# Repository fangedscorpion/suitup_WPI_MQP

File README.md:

# suitup_WPI_MQP
Repo for the WPI MQP project for Chas Frick, Matt Beardsley, Samee Swartz, Will Barnard, Amanda Adkins

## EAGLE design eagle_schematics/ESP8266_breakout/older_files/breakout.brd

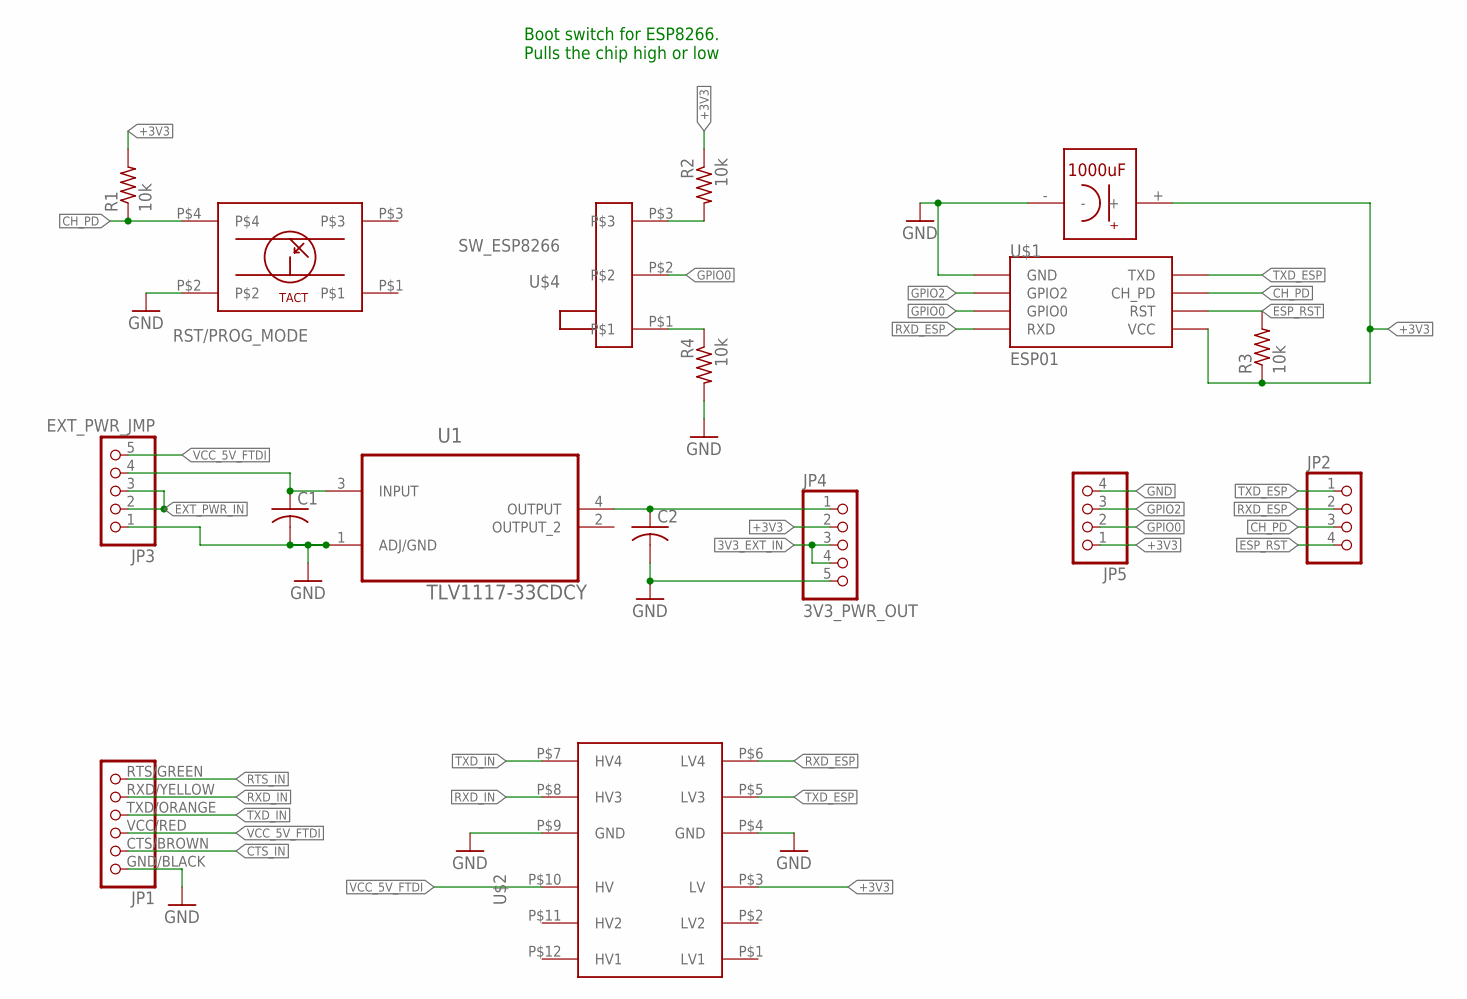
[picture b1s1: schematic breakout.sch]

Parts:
C1, C2: C-USC0805K; C0805K
JP1: FTDI_CABLE; FTDI_5V_SPARKFUN
JP2, JP5: PINHD-1X4; 1X04
JP3: EXT_PWR_JMP; 1X05
JP4: 3V3_PWR_OUT; 1X05
R1, R2, R3, R4: 10k; R1206
RST/PROG_MODE: TACT_SWITCH; TACT
U1: TLV1117-33CDCY; SOT230P700X180-4N
U$1: ESP01
U$2: LVLSHIFTER; LVLSFT_PAC
U$3: TZVCAP; TZV1000M
U$4: SW_ESP8266; SW_PCB_ESP

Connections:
3V3_EXT_IN: JP4.3, JP4.4
+3V3: JP4.2, JP5.1, R1.2, R2.1, R3.1, U$1.VCC, U$2.P$3 (LV), U$3.+
CH_PD: JP2.3, R1.1, RST/PROG_MODE.P$4, U$1.CH_PD
CTS_IN: JP1.CTS/BROWN (2)
ESP_RST: JP2.4, R3.2, U$1.RST
EXT_PWR_IN: JP3.2, JP3.3
GND: C1.2, C2.2, JP1.GND/BLACK (1), JP3.1, JP4.5, JP5.4, R4.2, RST/PROG_MODE.P$2, U1.1 (ADJ/GND), U$1.GND, U$2.P$4 (GND), U$2.P$9 (GND), U$3.-
GPIO0: JP5.2, U$1.GPIO0, U$4.P$2
GPIO2: JP5.3, U$1.GPIO2
unnamed: C2.1, JP4.1, U1.4 (OUTPUT)
unnamed: C1.1, JP3.4, U1.3 (INPUT)
unnamed: R2.2, U$4.P$3
unnamed: R4.1, U$4.P$1
RTS_IN: JP1.RTS/GREEN (6)
RXD_ESP: JP2.2, U$1.RX (RXD), U$2.P$6 (LV4)
RXD_IN: JP1.RXD/YELLOW (5), U$2.P$8 (HV3)
TXD_ESP: JP2.1, U$1.TX (TXD), U$2.P$5 (LV3)
TXD_IN: JP1.TXD/ORANGE (4), U$2.P$7 (HV4)
VCC_5V_FTDI: JP1.VCC/RED (3), JP3.5, U$2.P$10 (HV)

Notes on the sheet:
Boot switch for ESP8266. Pulls the chip high or low

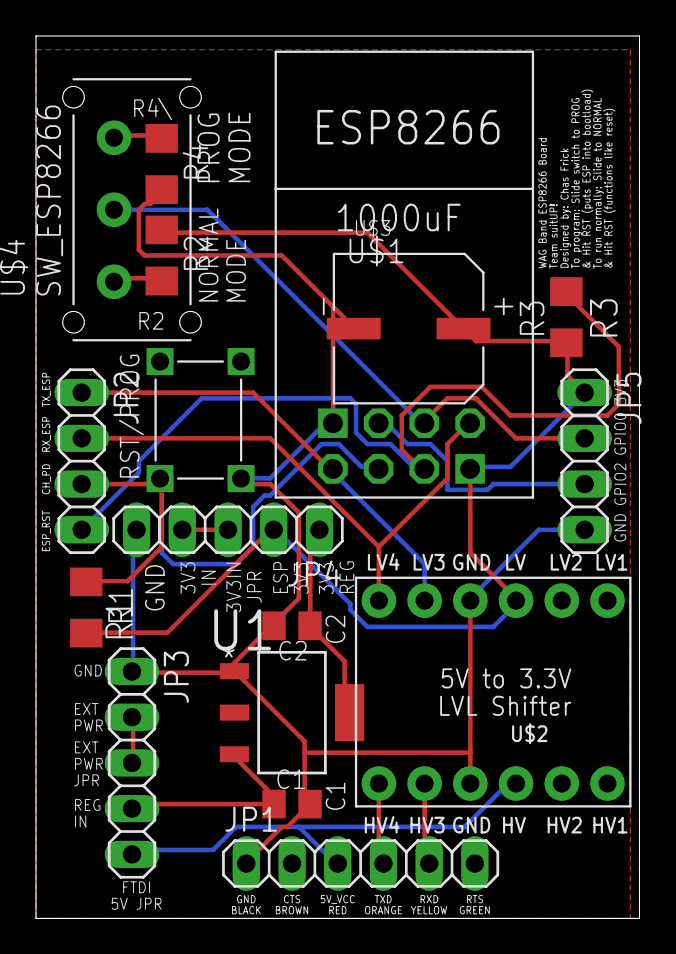
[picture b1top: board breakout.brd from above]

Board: 2 copper layers, 33.5 x 49.0 mm, 17 parts (0 on the bottom side), 17 nets.

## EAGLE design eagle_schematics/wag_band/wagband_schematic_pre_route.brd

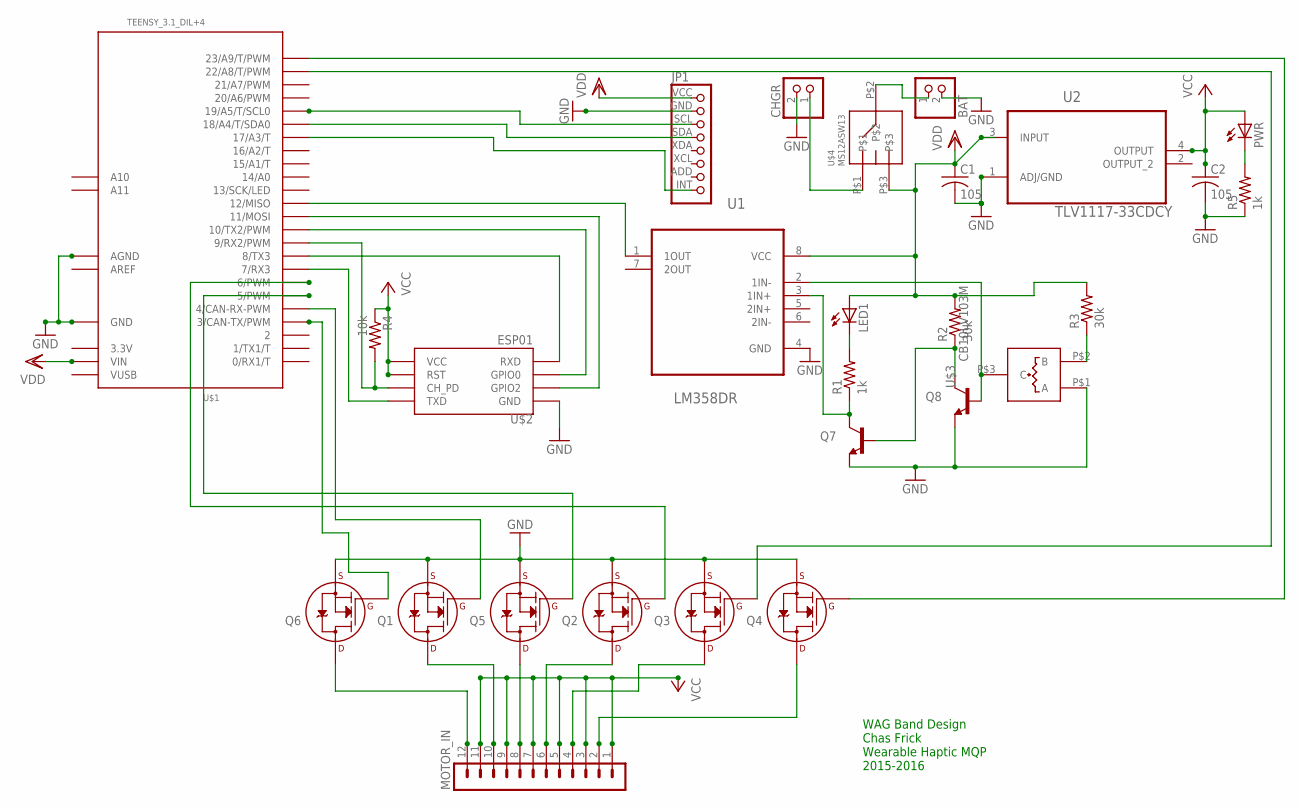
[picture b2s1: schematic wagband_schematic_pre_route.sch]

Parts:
BAT: JST_2PIN-THM-RA; JST-PH-2-THM-RA
C1, C2: 105; C0805K
CHGR: JST_2PIN-THM-RA; JST-PH-2-THM-RA
JP1: MPU6050_BREAKOUT; MPU6050
LED1: LED5MM
MOTOR_IN: MA12-1W
PWR: LED5MM
Q1, Q2, Q3, Q4, Q5, Q6: 2N7000_SOT23; SOT-23
Q7, Q8: TRANSISTOR_NPNMMBT3904; SOT-23
R1, R5: 1k; R1206
R2, R3: 30k; R1206
R4: 10k; R1206
U1: LM358DR; SOIC127P600X175-8N
U2: TLV1117-33CDCY; SOT230P700X180-4N
U$1: TEENSY_3.1_DIL+4; TEENSY3-DIL+4
U$2: ESP01
U$3: CB10LV103M; CB10
U$4: MS12ASW13; SPDT

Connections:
3.3V: U$1.3.3V
AREF: U$1.AREF
GND: BAT.2 (1), C1.2, C2.2, CHGR.2 (1), JP1.GND, Q1.2 (S), Q2.2 (S), Q3.2 (S), Q4.2 (S), Q5.2 (S), Q6.2 (S), Q7.2 (E), Q8.2 (E), R5.1, U1.4 (GND), U2.1 (ADJ/GND), U$1.AGND, U$1.GND, U$2.GND, U$3.P$1 (A)
unnamed: Q4.1 (G), U$1.23/A9 (23/A9/T/PWM)
unnamed: Q2.1 (G), U$1.6 (6/PWM)
unnamed: Q3.1 (G), U$1.22/A8 (22/A8/T/PWM)
unnamed: JP1.SDA, U$1.18/A4 (18/A4/T/SDA0)
unnamed: Q6.1 (G), U$1.3 (3/CAN-TX/PWM)
unnamed: Q1.1 (G), U$1.4 (4/CAN-RX-PWM)
unnamed: U$1.7 (7/RX3), U$2.TX (TXD)
unnamed: JP1.INT, U$1.17/A3 (17/A3/T)
unnamed: MOTOR_IN.12, Q6.3 (D)
unnamed: MOTOR_IN.10, Q1.3 (D)
unnamed: MOTOR_IN.8, Q5.3 (D)
unnamed: U$1.8 (8/TX3), U$2.RX (RXD)
unnamed: MOTOR_IN.6, Q2.3 (D)
unnamed: MOTOR_IN.2, Q4.3 (D)
unnamed: MOTOR_IN.4, Q3.3 (D)
unnamed: Q5.1 (G), U$1.5 (5/PWM)
unnamed: JP1.SCL, U$1.19/A5 (19/A5/T/SCL0)
unnamed: U$1.11 (11/MOSI), U$2.GPIO2
unnamed: U$1.10 (10/TX2/PWM), U$2.GPIO0
unnamed: Q7.3 (C), R1.1, U1.3 (1IN+)
unnamed: PWR.K (C), R5.2
unnamed: LED1.K (C), R1.2
unnamed: Q7.1 (B), Q8.3 (C), R2.1
unnamed: R4.2, U$1.9 (9/RX2/PWM), U$2.CH_PD
unnamed: Q8.1 (B), U1.2 (1IN-), U$3.P$3 (C)
unnamed: U1.1 (1OUT), U$1.12 (12/MISO)
unnamed: R3.1, U$3.P$2 (B)
unnamed: BAT.1 (2), U$4.P$2
unnamed: CHGR.1 (2), U$4.P$1
VCC: C2.1, MOTOR_IN.1, MOTOR_IN.3, MOTOR_IN.5, MOTOR_IN.7, MOTOR_IN.9, MOTOR_IN.11, PWR.A, R4.1, U2.4 (OUTPUT), U$2.RST, U$2.VCC
VDD: C1.1, JP1.VCC, LED1.A, R2.2, R3.2, U1.8 (VCC), U2.3 (INPUT), U$1.VIN, U$4.P$3
VUSB: U$1.VUSB

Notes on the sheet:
WAG Band Design Chas Frick Wearable Haptic MQP 2015-2016

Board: 2 copper layers, 27 parts (0 on the bottom side), 32 nets, no tracks yet.

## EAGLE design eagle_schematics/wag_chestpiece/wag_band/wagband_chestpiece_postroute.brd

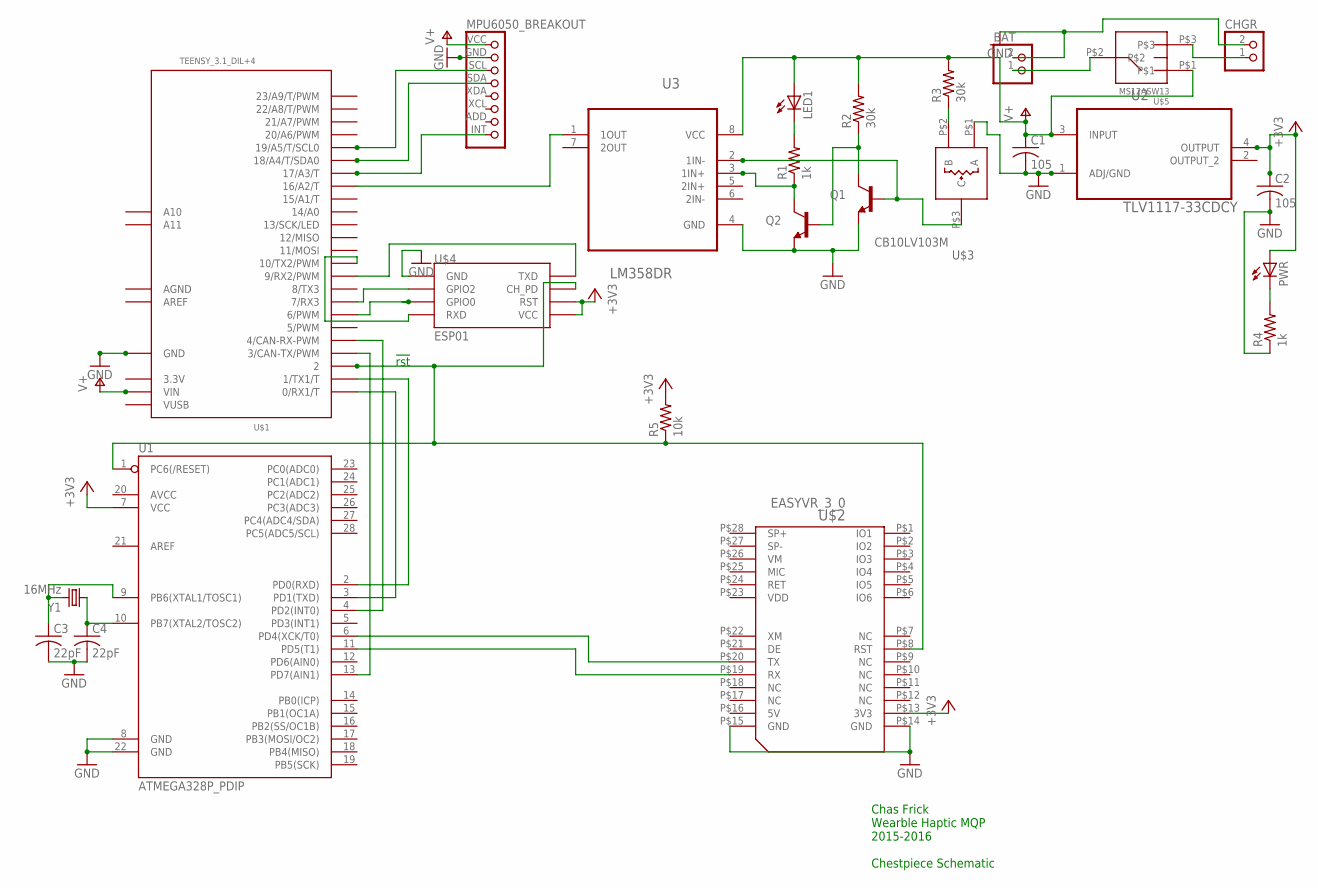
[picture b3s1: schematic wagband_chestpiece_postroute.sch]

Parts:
BAT: JST_2PIN-THM-RA; JST-PH-2-THM-RA
C1, C2: 105; C0805K
C3, C4: 22pF; C1206K
CHGR: JST_2PIN-THM-RA; JST-PH-2-THM-RA
LED1: LED5MM
MPU6050_BREAKOUT: MPU6050_BREAKOUT; MPU6050
PWR: LED5MM
Q1, Q2: TRANSISTOR_NPNMMBT3904; SOT-23
R1, R4: 1k; R1206
R2, R3: 30k; R1206
R5: 10k; R1206
U1: ATMEGA328P_PDIP; DIL28-3
U2: TLV1117-33CDCY; SOT230P700X180-4N
U3: LM358DR; SOIC127P600X175-8N
U$1: TEENSY_3.1_DIL+4; TEENSY3-DIL+4
U$2: EASYVR_3_0
U$3: CB10LV103M; CB10
U$4: ESP01
U$5: MS12ASW13; SPDT
Y1: 16MHz; HC49UP

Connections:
3.3V: U$1.3.3V
5V: U$2.P$16 (5V)
!RST: R5.1, U1.1 (PC6(/RESET)), U$1.2, U$2.P$8 (RST), U$4.CH_PD
+3V3: C2.1, PWR.A, R5.2, U1.7 (VCC), U2.4 (OUTPUT), U$2.P$13 (3V3), U$4.RST, U$4.VCC
AGND: U$1.AGND
AREF: U$1.AREF
GND: BAT.2 (1), C1.2, C2.2, C3.2, C4.2, CHGR.2 (1), MPU6050_BREAKOUT.GND, Q1.2 (E), Q2.2 (E), R4.1, U1.8 (GND), U1.22 (GND), U2.1 (ADJ/GND), U3.4 (GND), U$1.GND, U$2.P$14 (GND), U$2.P$15 (GND), U$3.P$1 (A), U$4.GND
unnamed: U1.4 (PD2(INT0)), U$1.4 (4/CAN-RX-PWM)
unnamed: U$1.10 (10/TX2/PWM), U$4.RX (RXD)
unnamed: MPU6050_BREAKOUT.SDA, U$1.18/A4 (18/A4/T/SDA0)
unnamed: Q1.1 (B), U3.2 (1IN-), U$3.P$3 (C)
unnamed: U1.11 (PD5(T1)), U$2.P$19 (RX)
unnamed: U1.6 (PD4(XCK/T0)), U$2.P$20 (TX)
unnamed: MPU6050_BREAKOUT.INT, U$1.17/A3 (17/A3/T)
unnamed: Q1.3 (C), Q2.1 (B), R2.1
unnamed: Q2.3 (C), R1.1, U3.3 (1IN+)
unnamed: R3.1, U$3.P$2 (B)
unnamed: LED1.K (C), R1.2
unnamed: U1.2 (PD0(RXD)), U$1.1 (1/TX1/T)
unnamed: U3.1 (1OUT), U$1.16/A2 (16/A2/T)
unnamed: PWR.K (C), R4.2
unnamed: U1.13 (PD7(AIN1)), U$1.3 (3/CAN-TX/PWM)
unnamed: MPU6050_BREAKOUT.SCL, U$1.19/A5 (19/A5/T/SCL0)
unnamed: U$1.6 (6/PWM), U$4.GPIO0
unnamed: U$1.9 (9/RX2/PWM), U$4.TX (TXD)
unnamed: C3.1, U1.9 (PB6(XTAL1/TOSC1)), Y1.2
unnamed: C4.1, U1.10 (PB7(XTAL2/TOSC2)), Y1.1
unnamed: U1.3 (PD1(TXD)), U$1.0 (0/RX1/T)
unnamed: BAT.1 (2), U$5.P$2
unnamed: U$1.7 (7/RX3), U$4.GPIO2
unnamed: CHGR.1 (2), U$5.P$3
V+: C1.1, LED1.A, MPU6050_BREAKOUT.VCC, R2.2, R3.2, U2.3 (INPUT), U3.8 (VCC), U$1.VIN, U$5.P$1
VDD: U$2.P$23 (VDD)
VUSB: U$1.VUSB

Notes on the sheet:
!rst
Chas Frick Wearble Haptic MQP 2015-2016 Chestpiece Schematic

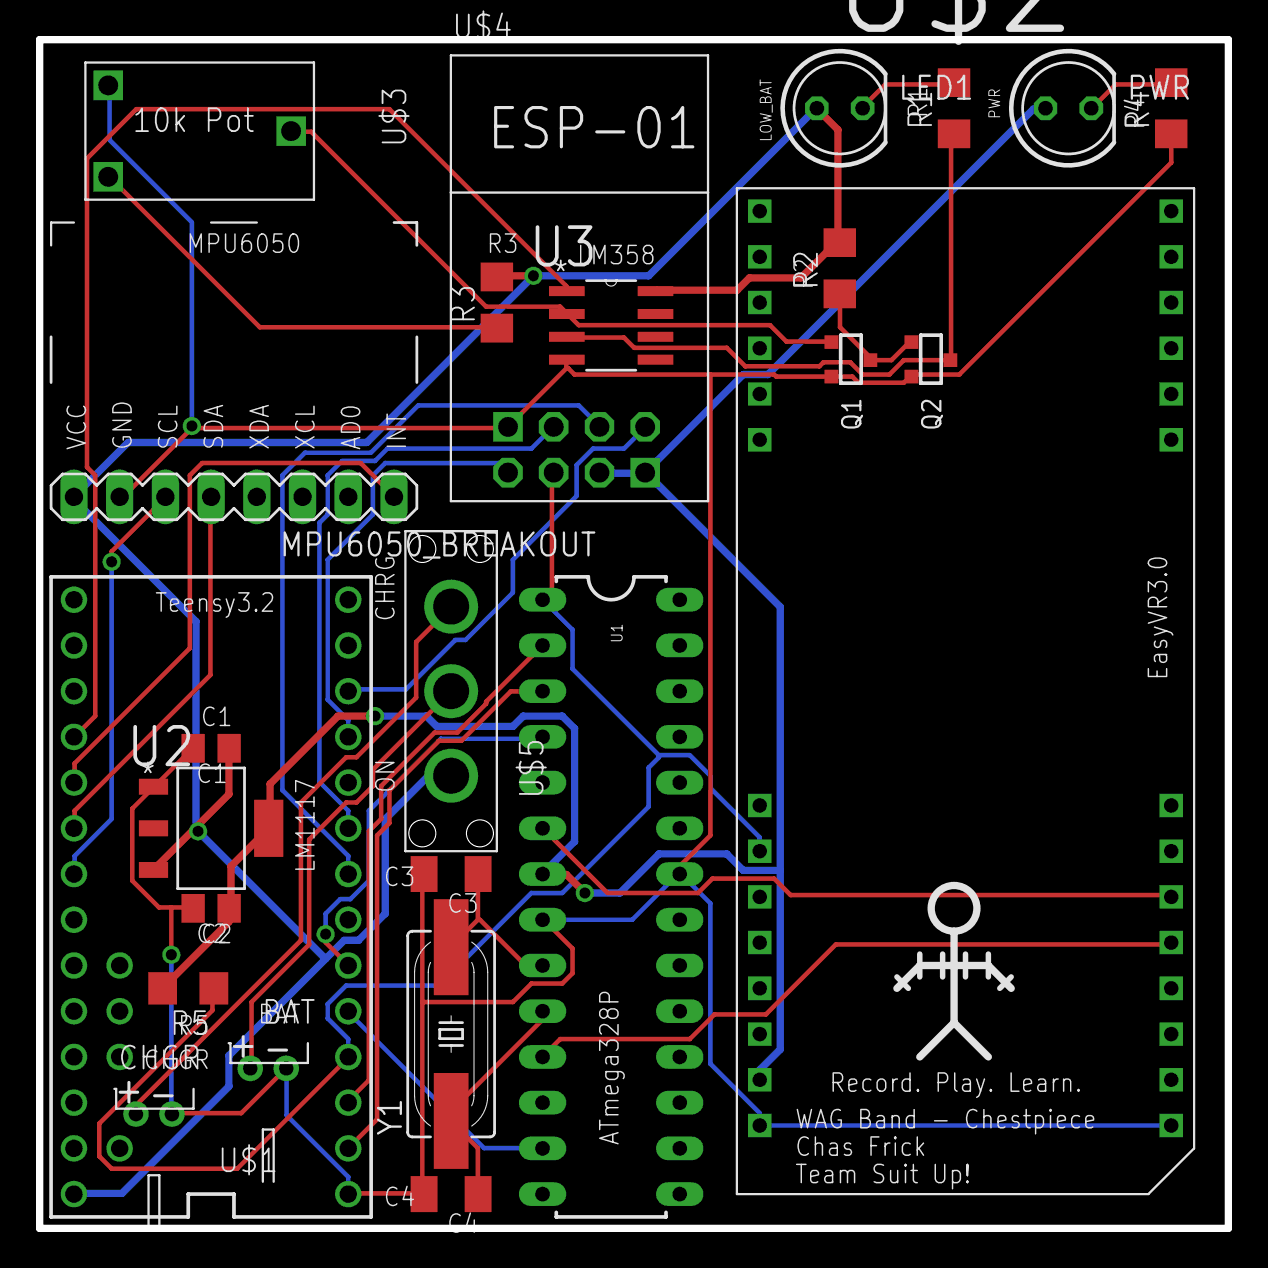
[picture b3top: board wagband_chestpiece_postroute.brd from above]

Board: 2 copper layers, 66.0 x 66.0 mm, 25 parts (0 on the bottom side), 28 nets.

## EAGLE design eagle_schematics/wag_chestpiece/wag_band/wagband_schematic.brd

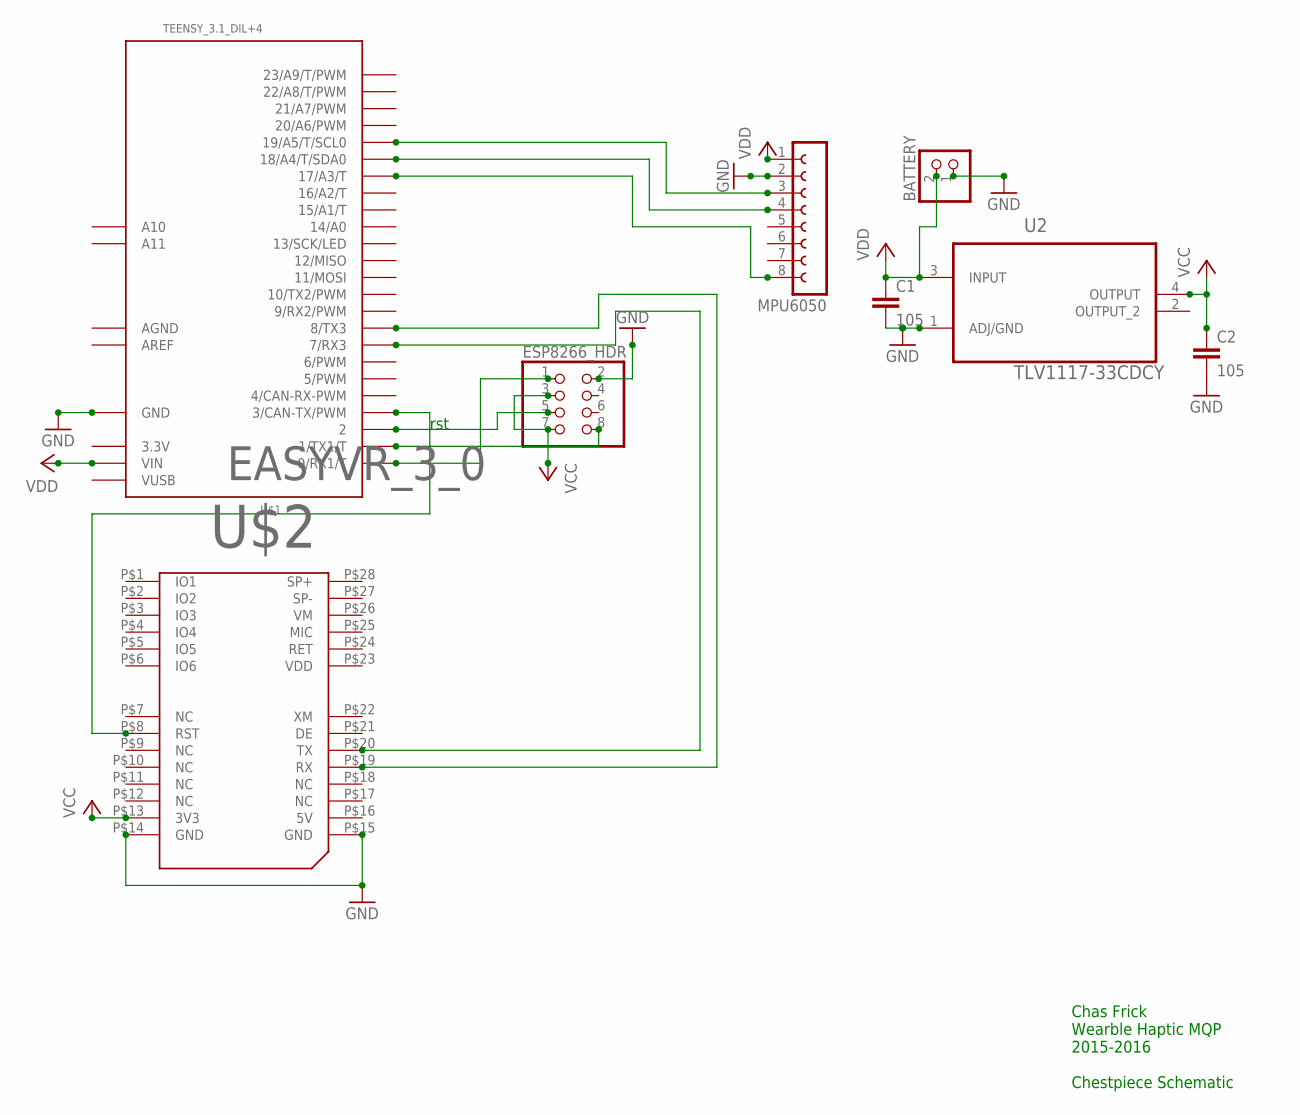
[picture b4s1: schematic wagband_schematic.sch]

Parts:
BATTERY: JST_2PIN-THM-RA; JST-PH-2-THM-RA
C1, C2: 105; C025-024X044
ESP8266_HDR: PINHD-2X4; 2X04
MPU6050: FE08-1; FE08
U2: TLV1117-33CDCY; SOT230P700X180-4N
U$1: TEENSY_3.1_DIL+4; TEENSY3-DIL+4
U$2: EASYVR_3_0

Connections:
3.3V: U$1.3.3V
5V: U$2.P$16 (5V)
AGND: U$1.AGND
AREF: U$1.AREF
GND: BATTERY.1 (2), C1.2, C2.2, ESP8266_HDR.2, MPU6050.2, U2.1 (ADJ/GND), U$1.GND, U$2.P$14 (GND), U$2.P$15 (GND)
unnamed: U$1.7 (7/RX3), U$2.P$20 (TX)
unnamed: U$1.8 (8/TX3), U$2.P$19 (RX)
unnamed: MPU6050.4, U$1.18/A4 (18/A4/T/SDA0)
unnamed: U$1.3 (3/CAN-TX/PWM), U$2.P$8 (RST)
unnamed: ESP8266_HDR.1, U$1.0 (0/RX1/T)
unnamed: MPU6050.8, U$1.17/A3 (17/A3/T)
unnamed: MPU6050.3, U$1.19/A5 (19/A5/T/SCL0)
unnamed: ESP8266_HDR.8, U$1.1 (1/TX1/T)
unnamed: ESP8266_HDR.5, U$1.2
VCC: BATTERY.2 (1), C1.1, C2.1, ESP8266_HDR.3, ESP8266_HDR.7, MPU6050.1, U2.3 (INPUT), U2.4 (OUTPUT), U$1.VIN, U$2.P$13 (3V3)
VDD: U$2.P$23 (VDD)
VUSB: U$1.VUSB

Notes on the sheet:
rst
Chas Frick Wearble Haptic MQP 2015-2016 Chestpiece Schematic

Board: 2 copper layers, 8 parts (0 on the bottom side), 11 nets, no tracks yet.

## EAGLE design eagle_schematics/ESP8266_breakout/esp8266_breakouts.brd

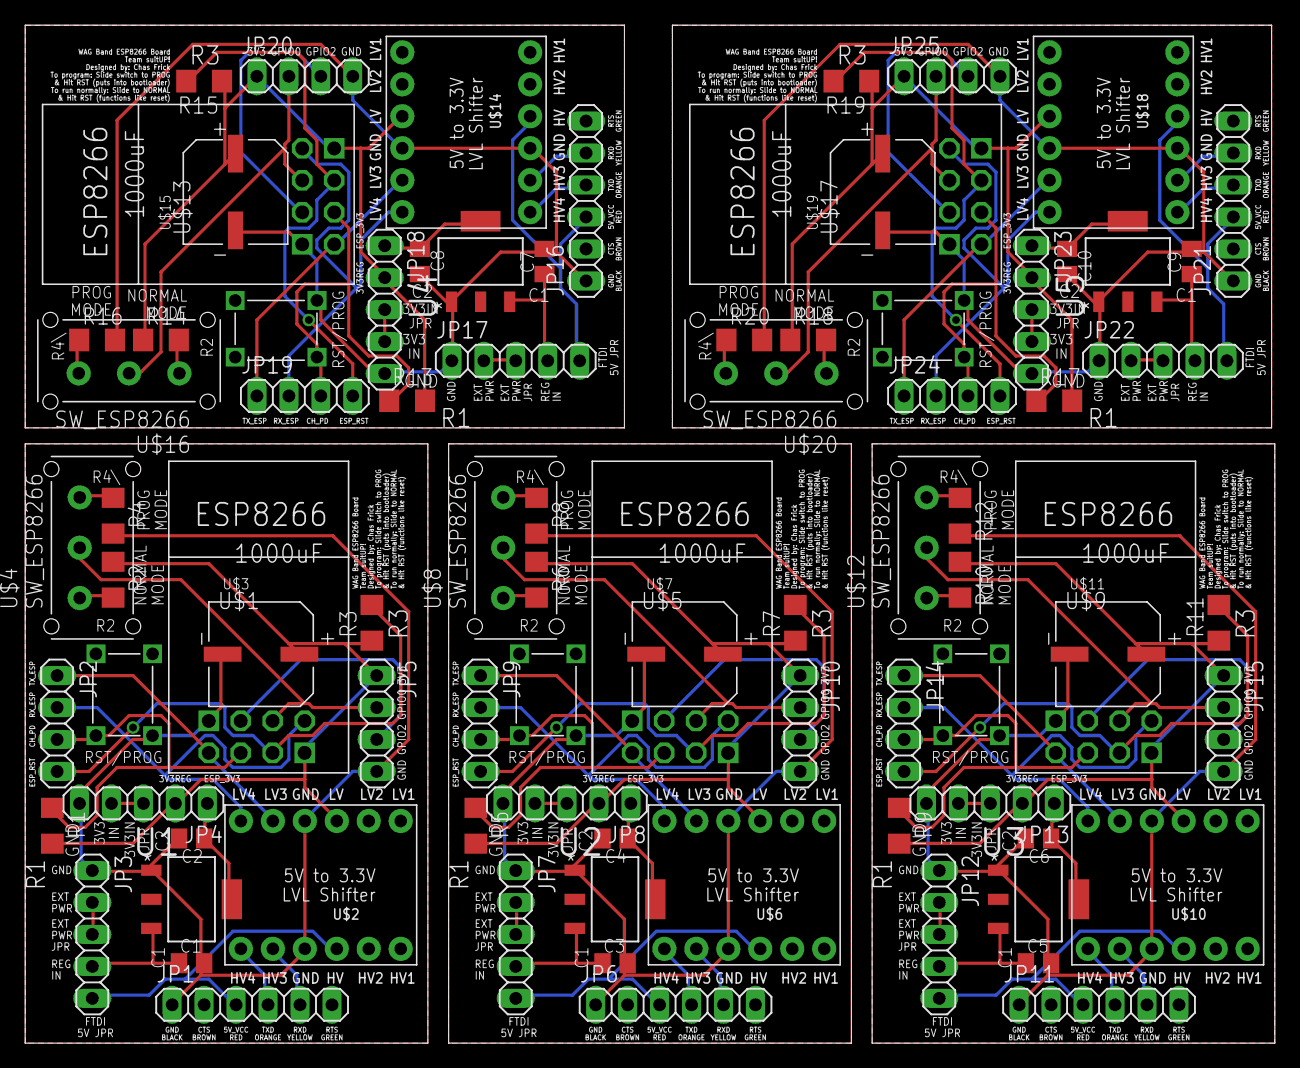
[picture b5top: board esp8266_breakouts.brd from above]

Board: 2 copper layers, 99.3 x 80.9 mm, 85 parts (0 on the bottom side), 85 nets.

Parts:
C1, C2, C3, C4, C5, C6, C7, C8, C9, C10: C0805K
JP1, JP6, JP11, JP16, JP21: FTDI_5V_SPARKFUN
JP2, JP5, JP9, JP10, JP14, JP15, JP19, JP20, JP24, JP25: 1X04
JP3, JP7, JP12, JP17, JP22: EXT_PWR_JMP; 1X05
JP4, JP8, JP13, JP18, JP23: 3V3_PWR_OUT; 1X05
R1, R2, R3, R4, R5, R6, R7, R8, R9, R10, R11, R12, R13, R14, R15, R16, R17, R18, R19, R20: 10k; R1206
RST/PROG_MODE, RST/PROG_MODE1, RST/PROG_MODE2, RST/PROG_MODE3, RST/PROG_MODE4: TACT_SWITCH; TACT
U1, U2, U3, U4, U5: TLV1117-33CDCY; SOT230P700X180-4N
U$1, U$5, U$9, U$13, U$17: ESP01
U$2, U$6, U$10, U$14, U$18: LVLSHIFTER; LVLSFT_PAC
U$3, U$7, U$11, U$15, U$19: TZVCAP; TZV1000M
U$4, U$8, U$12, U$16, U$20: SW_ESP8266; SW_PCB_ESP

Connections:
3V3_EXT_IN: JP4.3, JP4.4
3V3_EXT_IN1: JP8.3, JP8.4
3V3_EXT_IN2: JP13.3, JP13.4
3V3_EXT_IN3: JP18.3, JP18.4
3V3_EXT_IN4: JP23.3, JP23.4
+3V1: JP8.2, JP10.1, R5.2, R6.1, R7.1, U$5.VCC, U$6.P$3, U$7.+
+3V2: JP13.2, JP15.1, R9.2, R10.1, R11.1, U$9.VCC, U$10.P$3, U$11.+
+3V3: JP4.2, JP5.1, R1.2, R2.1, R3.1, U$1.VCC, U$2.P$3, U$3.+
+3V4: JP18.2, JP20.1, R13.2, R14.1, R15.1, U$13.VCC, U$14.P$3, U$15.+
+3V5: JP23.2, JP25.1, R17.2, R18.1, R19.1, U$17.VCC, U$18.P$3, U$19.+
CH_PD: JP2.3, R1.1, RST/PROG_MODE.P$4, U$1.CH_PD
CH_PD1: JP9.3, R5.1, RST/PROG_MODE1.P$4, U$5.CH_PD
CH_PD2: JP14.3, R9.1, RST/PROG_MODE2.P$4, U$9.CH_PD
CH_PD3: JP19.3, R13.1, RST/PROG_MODE3.P$4, U$13.CH_PD
CH_PD4: JP24.3, R17.1, RST/PROG_MODE4.P$4, U$17.CH_PD
ESP_RST: JP2.4, R3.2, U$1.RST
ESP_RST1: JP9.4, R7.2, U$5.RST
ESP_RST2: JP14.4, R11.2, U$9.RST
ESP_RST3: JP19.4, R15.2, U$13.RST
ESP_RST4: JP24.4, R19.2, U$17.RST
EXT_PWR_IN: JP3.2, JP3.3
EXT_PWR_IN1: JP7.2, JP7.3
EXT_PWR_IN2: JP12.2, JP12.3
EXT_PWR_IN3: JP17.2, JP17.3
EXT_PWR_IN4: JP22.2, JP22.3
GND: C1.2, C2.2, JP1.GND/BLACK, JP3.1, JP4.5, JP5.4, R4.2, RST/PROG_MODE.P$2, U1.1, U$1.GND, U$2.P$4, U$2.P$9, U$3.-
GND1: C3.2, C4.2, JP6.GND/BLACK, JP7.1, JP8.5, JP10.4, R8.2, RST/PROG_MODE1.P$2, U2.1, U$5.GND, U$6.P$4, U$6.P$9, U$7.-
GND2: C5.2, C6.2, JP11.GND/BLACK, JP12.1, JP13.5, JP15.4, R12.2, RST/PROG_MODE2.P$2, U3.1, U$9.GND, U$10.P$4, U$10.P$9, U$11.-
GND3: C7.2, C8.2, JP16.GND/BLACK, JP17.1, JP18.5, JP20.4, R16.2, RST/PROG_MODE3.P$2, U4.1, U$13.GND, U$14.P$4, U$14.P$9, U$15.-
GND4: C9.2, C10.2, JP21.GND/BLACK, JP22.1, JP23.5, JP25.4, R20.2, RST/PROG_MODE4.P$2, U5.1, U$17.GND, U$18.P$4, U$18.P$9, U$19.-
GPIO0: JP5.2, U$1.GPIO0, U$4.P$2
GPIO1: JP10.2, U$5.GPIO0, U$8.P$2
GPIO2: JP5.3, U$1.GPIO2
GPIO3: JP10.3, U$5.GPIO2
GPIO4: JP15.2, U$9.GPIO0, U$12.P$2
GPIO5: JP15.3, U$9.GPIO2
GPIO6: JP20.2, U$13.GPIO0, U$16.P$2
GPIO7: JP20.3, U$13.GPIO2
GPIO8: JP25.2, U$17.GPIO0, U$20.P$2
GPIO9: JP25.3, U$17.GPIO2
unnamed: C2.1, JP4.1, U1.4
unnamed: C1.1, JP3.4, U1.3
unnamed: C3.1, JP7.4, U2.3
unnamed: R2.2, U$4.P$3
unnamed: C4.1, JP8.1, U2.4
unnamed: R4.1, U$4.P$1
unnamed: R6.2, U$8.P$3
unnamed: R8.1, U$8.P$1
unnamed: C5.1, JP12.4, U3.3
unnamed: C6.1, JP13.1, U3.4
unnamed: R10.2, U$12.P$3
unnamed: R12.1, U$12.P$1
unnamed: C7.1, JP17.4, U4.3
unnamed: C8.1, JP18.1, U4.4
unnamed: R14.2, U$16.P$3
unnamed: R16.1, U$16.P$1
unnamed: C9.1, JP22.4, U5.3
unnamed: C10.1, JP23.1, U5.4
unnamed: R18.2, U$20.P$3
unnamed: R20.1, U$20.P$1
RXD_ESP: JP2.2, U$1.RX, U$2.P$6
RXD_ESP1: JP9.2, U$5.RX, U$6.P$6
RXD_ESP2: JP14.2, U$9.RX, U$10.P$6
RXD_ESP3: JP19.2, U$13.RX, U$14.P$6
RXD_ESP4: JP24.2, U$17.RX, U$18.P$6
RXD_IN: JP1.RXD/YELLOW, U$2.P$8
RXD_IN1: JP6.RXD/YELLOW, U$6.P$8
RXD_IN2: JP11.RXD/YELLOW, U$10.P$8
RXD_IN3: JP16.RXD/YELLOW, U$14.P$8
RXD_IN4: JP21.RXD/YELLOW, U$18.P$8
TXD_ESP: JP2.1, U$1.TX, U$2.P$5
TXD_ESP1: JP9.1, U$5.TX, U$6.P$5
TXD_ESP2: JP14.1, U$9.TX, U$10.P$5
TXD_ESP3: JP19.1, U$13.TX, U$14.P$5
TXD_ESP4: JP24.1, U$17.TX, U$18.P$5
TXD_IN: JP1.TXD/ORANGE, U$2.P$7
TXD_IN1: JP6.TXD/ORANGE, U$6.P$7
TXD_IN2: JP11.TXD/ORANGE, U$10.P$7
TXD_IN3: JP16.TXD/ORANGE, U$14.P$7
TXD_IN4: JP21.TXD/ORANGE, U$18.P$7
VCC_5V_FTDI: JP1.VCC/RED, JP3.5, U$2.P$10
VCC_5V_FTDI1: JP6.VCC/RED, JP7.5, U$6.P$10
VCC_5V_FTDI2: JP11.VCC/RED, JP12.5, U$10.P$10
VCC_5V_FTDI3: JP16.VCC/RED, JP17.5, U$14.P$10
VCC_5V_FTDI4: JP21.VCC/RED, JP22.5, U$18.P$10

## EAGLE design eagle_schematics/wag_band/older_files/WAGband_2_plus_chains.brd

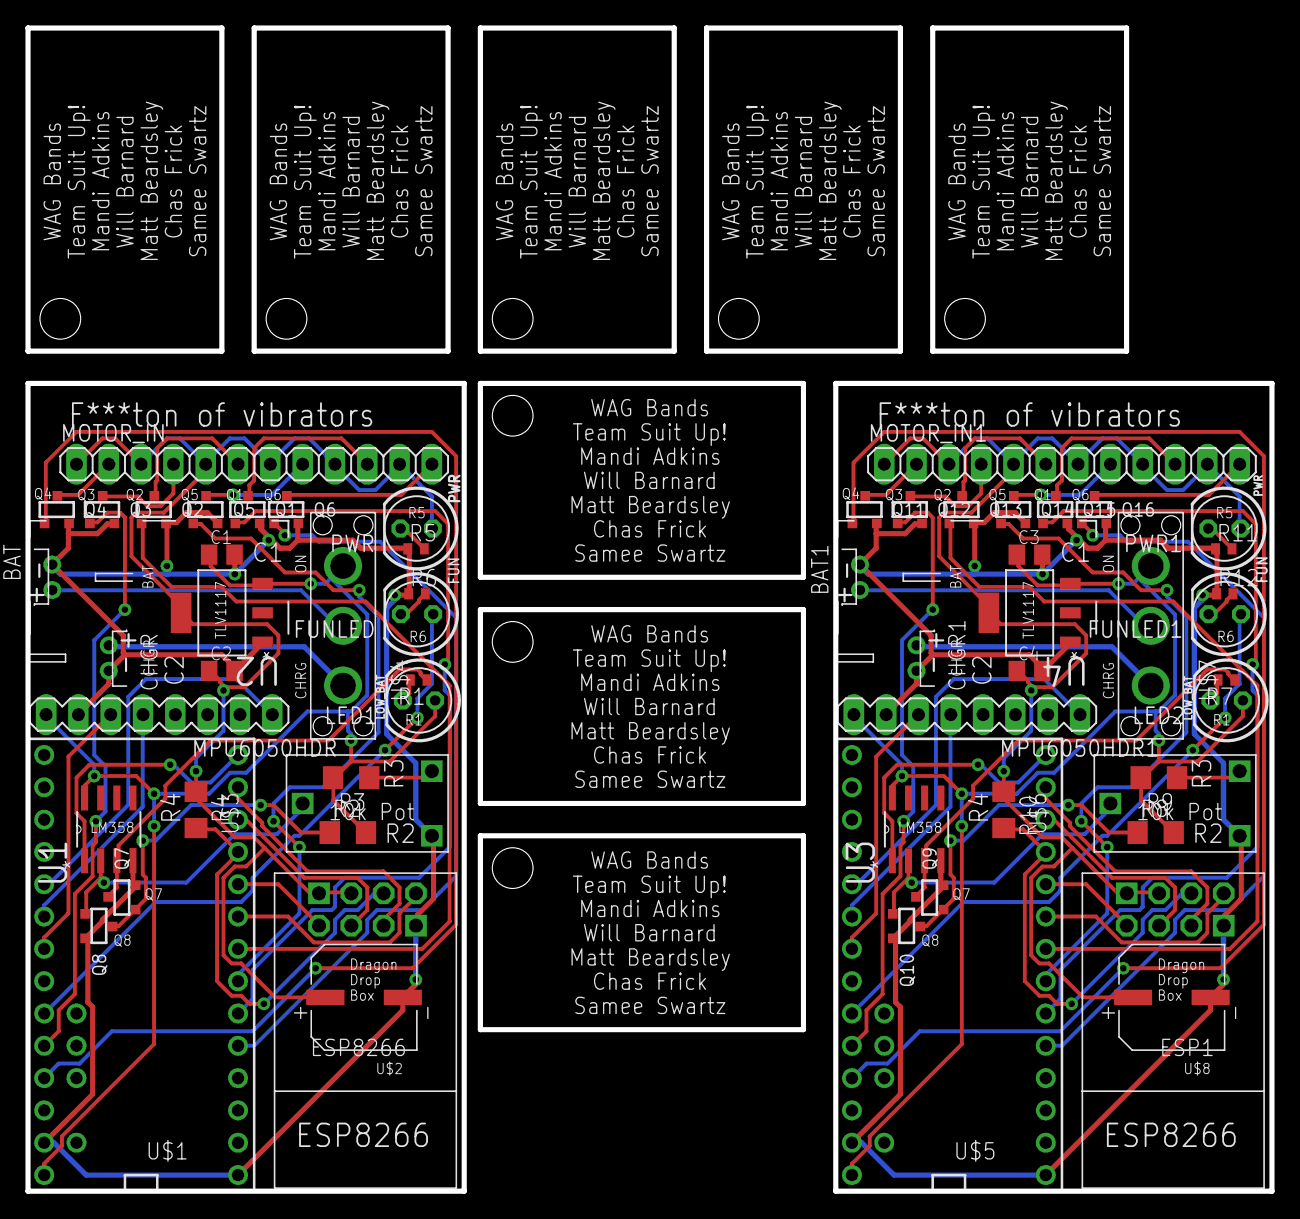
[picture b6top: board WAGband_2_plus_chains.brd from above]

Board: 2 copper layers, 97.8 x 91.4 mm, 60 parts (0 on the bottom side), 68 nets.

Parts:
BAT, BAT1: JST-PH-2-THM-RA
C1, C2, C3, C4: 105; C0805K
CHGR, CHGR1: JST-PH-2-THM-RA
ESP1, ESP8266: ESP01
FUNLED, FUNLED1: LED5MM
LED1, LED2: LED5MM
MOTOR_IN, MOTOR_IN1: 1X12
MPU6050HDR, MPU6050HDR1: MPU6050
PWR, PWR1: LED5MM
Q1, Q2, Q3, Q4, Q5, Q6, Q7, Q8, Q9, Q10, Q11, Q12, Q13, Q14, Q15, Q16: SOT-23
R1, R5, R6, R7, R11, R12: 1k; R0402
R2, R3, R8, R9: 30k; R1206
R4, R10: 10k; R1206
U1, U3: LM358DR; SOIC127P600X175-8N
U2, U4: TLV1117-33CDCY; SOT230P700X180-4N
U$1, U$5: TEENSY_3.1_DIL+4; TEENSY3-DIL+4
U$2, U$8: TZVCAP; TZV1000M
U$3, U$6: CB10LV103M; CB10
U$4, U$7: MS12ASW13; SPDT

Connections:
ESP8266_!RST: ESP8266.CH_PD, R4.2, U$1.9
ESP8266_!RST1: ESP1.CH_PD, R10.2, U$5.9
ESP8266_RX: ESP8266.RX, U$1.8
ESP8266_RX1: ESP1.RX, U$5.8
ESP8266_TX: ESP8266.TX, U$1.7
ESP8266_TX1: ESP1.TX, U$5.7
GND: BAT.2, C1.2, C2.2, CHGR.2, ESP8266.GND, MPU6050HDR.GND, Q1.2, Q2.2, Q3.2, Q4.2, Q5.2, Q6.2, Q7.2, Q8.2, R5.1, R6.1, U1.4, U2.1, U$1.AGND, U$1.GND, U$2.-, U$3.P$1
GND1: BAT1.2, C3.2, C4.2, CHGR1.2, ESP1.GND, MPU6050HDR1.GND, Q9.2, Q10.2, Q11.2, Q12.2, Q13.2, Q14.2, Q15.2, Q16.2, R11.1, R12.1, U3.4, U4.1, U$5.AGND, U$5.GND, U$6.P$1, U$8.-
GPIO0: ESP8266.GPIO0, U$1.10
GPIO1: ESP1.GPIO2, U$5.11
GPIO2: ESP8266.GPIO2, U$1.11
GPIO3: ESP1.GPIO0, U$5.10
LED_REF: Q7.3, R1.1, U1.3
LED_REF1: Q9.3, R7.1, U3.3
LOW_BATT_DIO: U1.1, U$1.12
LOW_BATT_DIO1: U3.1, U$5.12
M1: Q1.1, U$1.4
M2: Q2.1, U$1.6
M3: Q3.1, U$1.22/A8
M4: Q4.1, U$1.23/A9
M5: Q5.1, U$1.5
M6: Q6.1, U$1.3
M7: Q13.1, U$5.6
M8: Q14.1, U$5.5
M9: Q15.1, U$5.4
M10: Q16.1, U$5.3
M11: Q12.1, U$5.22/A8
M12: Q11.1, U$5.23/A9
unnamed: MPU6050HDR.INT, U$1.17/A3
unnamed: MPU6050HDR.SDA, U$1.18/A4
unnamed: FUNLED.A, U$1.21/A7
unnamed: FUNLED.K, R6.2
unnamed: MOTOR_IN1.12, Q16.3
unnamed: MOTOR_IN1.10, Q15.3
unnamed: MOTOR_IN.12, Q6.3
unnamed: MOTOR_IN.10, Q1.3
unnamed: MOTOR_IN.8, Q5.3
unnamed: MOTOR_IN1.8, Q14.3
unnamed: MOTOR_IN.6, Q2.3
unnamed: MOTOR_IN.2, Q4.3
unnamed: MOTOR_IN.4, Q3.3
unnamed: MOTOR_IN1.6, Q13.3
unnamed: MPU6050HDR.SCL, U$1.19/A5
unnamed: MOTOR_IN1.2, Q11.3
unnamed: MOTOR_IN1.4, Q12.3
unnamed: MPU6050HDR1.SCL, U$5.19/A5
unnamed: PWR.K, R5.2
unnamed: LED1.K, R1.2
unnamed: Q7.1, Q8.3, R2.1
unnamed: PWR1.K, R11.2
unnamed: LED2.K, R7.2
unnamed: Q9.1, Q10.3, R8.1
unnamed: R3.1, U$3.P$2
unnamed: BAT.1, U$4.P$2
unnamed: CHGR.1, U$4.P$1
unnamed: R9.1, U$6.P$2
unnamed: BAT1.1, U$7.P$2
unnamed: CHGR1.1, U$7.P$1
unnamed: MPU6050HDR1.INT, U$5.17/A3
unnamed: MPU6050HDR1.SDA, U$5.18/A4
unnamed: FUNLED1.K, R12.2
unnamed: FUNLED1.A, U$5.21/A7
POT_REF: Q8.1, U1.2, U$3.P$3
POT_REF1: Q10.1, U3.2, U$6.P$3
VCC: C2.1, ESP8266.RST, ESP8266.VCC, MOTOR_IN.1, MOTOR_IN.3, MOTOR_IN.5, MOTOR_IN.7, MOTOR_IN.9, MOTOR_IN.11, PWR.A, R4.1, U2.4, U$2.+
VCC1: C4.1, ESP1.RST, ESP1.VCC, MOTOR_IN1.1, MOTOR_IN1.3, MOTOR_IN1.5, MOTOR_IN1.7, MOTOR_IN1.9, MOTOR_IN1.11, PWR1.A, R10.1, U4.4, U$8.+
VDD: C1.1, LED1.A, MPU6050HDR.VCC, R2.2, R3.2, U1.8, U2.3, U$1.VIN, U$4.P$3
VDD1: C3.1, LED2.A, MPU6050HDR1.VCC, R8.2, R9.2, U3.8, U4.3, U$5.VIN, U$7.P$3

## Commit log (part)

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2015-11-17 new files yo
2015-11-17 Add rectangular prism and basic opengl widget to UI
2015-11-18 working kinematic model based on global orientation quaternions for each band location
2015-11-18 Add camera object for maintaining viewpoint in visualization; Add comments
2015-11-18 Add networking monitor (will be one attached to each band (I think))
2015-11-18 condense kinematic tree point generation into 1 for loop. muuuuuuch cleaner
2015-11-18 Fix network monitor class
2015-11-19 Added ESP8266 code
2015-11-19 Actually make light follow camera (hopefully)
2015-11-23 added settings GUI
2015-11-24 add swing/twist quaternion decomposition for error measurements
2015-11-28 make file works. follow the instructions on top
2015-11-28 added TestBand.h, made Arms, Hands, Shoulders check their incoming band type. Fixed Suit's constructor
2015-12-01 fixed compile error
2015-12-03 Updated server a bit
2015-12-04 Make other files reflect viz file reorganization
2015-12-04 Make vertex translator change reflect in glwidget and vertextranslator
2015-12-04 Convert gl module to accept indices instead of list of verticies
2015-12-04 Get adding vertices by index working; create function that allows to add plane defined by corner points and output plane
2015-12-04 Actually fix pro file (couldn't find tabcontent.cpp)
2015-12-04 change how stepthrough mode activation is handled; lock options during playback; slowly step through motion in visualization if suit is disabled and step through mode is enabled
2015-12-05 rotation and translation vibration scheme implemented for arduino
2015-12-05 my stuff
2015-12-11 Adding EasyVR library
    EasyVR library for voice recognition
2015-12-11 Add new feature to index.html
2015-12-11 Fix index.html agian
2015-12-11 Integrate drag functionality with main webpage
2015-12-12 Update website to include enhanced drag functionality
2015-12-15 background is fancy af
2015-12-15 (intentionally shitty commit comment goes here)
2015-12-16 Update index.html
    Old image: http://i.imgur.com/T6baft7.png
2015-12-18 Added code to interface Arduino to Teensy
    The Arduino communicates to the Teensy over SoftwareSerial on Pins 10
    (RX) and Pin 11 (TX). Serial1 on the Teensy is used to communicate to
    receive the bytes from the Arduino
2015-12-31 stuff
2016-01-02 working main windows
2016-01-07 Update website links
2016-01-07 I think links should actually all work this time
2016-01-07 update team website
2016-01-17 make band classes compile by commenting out print line; determine sending band based on source port; start wifiManager listening in mainWindow; add function for sending data to a desired band (untest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
2016-01-18 created WAGFile to hold wag file information
2016-01-19 Make bash script for installing needed libraries
2016-01-24 Started conversion from computer as server to computer as client; removed abshapticgenerator given that haptic decisions made on band to reduce data required to transmit; Work TODO: enable slot for c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
2016-01-24 remove some unused code; populate ip and port maps; TODO: error checking/slot to recv errors; determine how to retry if connection attempt fails, and when to give up retrying; fill in message interpr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
2016-01-26 update the band/suit classes that actually get used!
2016-01-27 added validation check to editMotionInfo
2016-01-31 Eagle schematic for chestpiece
    Added new chestpiece with larger traces and everything good
2016-02-03 made GUI larger
2016-02-05 Remove unused classes; integrate message protocol and format into wifiManager; move testing echo in reverse code to suit class; add testing server to output message transmitted and simulate hardware 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
2016-02-05 Update mock-band server; implement 5 second pings while not playing or recording in computer application
2016-02-08 add kinematics
2016-02-08 added motionViewer class
2016-02-08 NOW no more segfault
2016-02-08 update error calculation
2016-02-09 add error interface and quaternion error implementation
2016-02-10 Merged motion.cpp into wagfile.cpp; connected go to frame to retrieve a position snapshot from the set motion; removed print lines and commented out code; passed suit object into created tabs; passed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
2016-02-11 Change port numbers to have single ip; leave in old ones commented out for testing via command line or if we decide not to have static IPs any more
2016-02-11 Updated echoServer to dynamically allow for server port selection and played with TCP junk
2016-02-11 tests! implement vector and quaternion reflection tests
2016-02-12 Updating ESP8266 Code
    Still many function prototypes left to implement. To Matt if you read
    this I'm sorry for pulling a Jessie and committing broken code, but this
    is the best way to tell me what I still need to do (because I can't test
    all the wifi packets yet). Also adding more to the header file for msg
    types to include a low battery message
2016-02-12 created status labels
2016-02-15 Change all time references to qint32 instead of 64, add basic handling for position delivery; DOES NOT COMPILE
2016-02-17 test pose objects. pointers are hard.
2016-02-18 add pretty comprehensive pose object tests. rewrite error function. take care of some memory leaks. add some trivial getter functions
2016-02-18 Fix things that wouldn't compile; still need to deserialize pose
2016-02-19 created new label for tags. almost there
2016-02-19 Playback and recording should be implemented now
2016-02-19 update IError withinTolerance method
2016-02-19 Remove case statements from switch statements in bands so that position updates actually get to super class; remove unused code & outdated comments
2016-02-19 OMG. CloseableLabels are done! They even save with files. woot
2016-02-22 Make file for easily switching between testing locally and using with bands; somewhat update testing band server (timer for sending fake quaternions doesn't seem to work, but everything else seems to)
2016-02-22 change range of swing error from interval [-1,1] to [0,1]
2016-02-23 made it perty
2016-02-23 add original blender biped, fix .pro? or maybe it was just .pro.user, who knows
2016-02-23 undo bad assimp attempt on simple/minimal opengl example
2016-02-23 Have something for emitting what position the current bar on the slider should be at; reduce the wait time for the select call
2016-02-24 tried some more model export formats. a single .obj/.3ds or several .ply files seem like the best representations. add some notes on how to perform the transformations for opengl too
2016-02-24 spinny thing sorry this commit comment is garbo
2016-02-24 working on saving to 'library'. not working yet
2016-02-25 Change from pointer to qset to qset obj
2016-02-25 fix/finalize body model including normal directions, replace arbitrary scaling/normalization with camera placement adjustments
2016-02-25 Huge commit milestron
2016-02-26 update python script to export blender model as obj/mtl
2016-02-26 got a pretty 'open from lib' selector. It doesn't actually open the selected file yet
2016-02-29 finished open from lib widget
2016-02-29 open from lib filter bar works
2016-03-01 Add code for changing labels given qint32 representing time in millis; rework positionsnapshot retreival to try to make it faster
2016-03-01 Revise ping timeouts so that mulitple pings have to be missed for the band to be considered 'disconnected'
2016-03-02 comment out most printlines involved in receiving - still need a printline in the message handling part... dont know why
2016-03-02 Because something can disconnect in multiple ways, have to keep track of which ones are/aren't connected; implemented in main window so we don't get multiple disconnections for one band if the band m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
2016-03-07 small bug fixes
2016-03-07 refactoring
2016-03-08 fixed another bug
2016-03-10 Resurrecting this from the dead as it was deleted and is back now after Trump killed it. Good luck rerouting the board from this!
2016-03-11 Something that is so much better works finally. I think
    https://github.com/esp8266/Arduino/issues/385 Really helped me out here
2016-03-12 integrate updated glwidget into main application
2016-03-12 add to install script
2016-03-13 color scheme!
2016-03-13 added 'all' to lib search
2016-03-13 fixed checkboxes and made labels consistant with the style
2016-03-14 Add print line, make install script executable
2016-03-15 don't remember...
2016-03-15 Add .wagz files to gitignore
2016-03-15 add some prints for debugging
2016-03-15 Semifix low battery & voice control in recording mode; need to fix voice control in playback mode, update low battery processing to reduce signals emitted, and investigate if AbsStates are properly s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
2016-03-15 Low battery notifications should be improved and working now --- still need to test; Voice control in playback mode should also theoretically work now -- also pending testing
2016-03-16 add node to abspose for pose tracking, restore abspose update/calibrate functionality with node
2016-03-17 testing with a moc band gives me so many segfaults...
2016-03-20 fix some compiler warnings. all that's left are unused parameter and unused variable warnings
2016-03-23 working on converting most * to QPointers
2016-03-23 put limit on number of iterations it'll parse for (should probably be less than this, but just wanted some limit for now
2016-03-24 Fixed the Voice Recognition on the ChestPiece
    Had to install the 8MHz breadboard arduino library and program that via
    an empty arduino socket. But it's on the board and the chestband works
    to the Teensy. Oooh rah baby
2016-03-24 remove settings shadow to fix weird pixellation, add 2nd glwidget (1st glwidget to show calibration pose, 2nd glwidget to show what the software thinks the suit's pose is)
2016-03-25 Prevent segfaulting when position data received when not collecting
2016-03-26 everything but layouts have parent, child relations. layouts fuck shit up.
2016-03-26 Compiled the code for the Chest Piece and uploaded to the board
    This is the code for the working chestpiece and some other small tweaks
2016-03-27 Just kidding; was too over eager to commit and missed build error; please forgive me git gods
2016-03-31 Enable suit to know if it's on settings window; if suit is on settings window and receives band_connected message; tell it to start recording for calibration purposes
2016-04-01 fix QByteArray sign issue for data reading
2016-04-03 all valigrind errors are gonegit pull origin qtCreator !
2016-04-03 more memory leaks fixed
2016-04-03 Updated playback mode to include a reset condition (to stop the motors)
2016-04-04 Add GIF functionality to beautiful website
2016-04-04 middebugging
2016-04-05 crop is implemented, but not tested
2016-04-07 Disable testing mode
2016-04-08 Fix step through mode preview
2016-04-10 Theoretically enable voice calibrationn
2016-04-11 Fix segfaults
2016-04-12 Invalidate bands whens tarting and stopping; add more information to printlines
2016-04-12 not testing
2016-04-14 Adding two files that load and playback well. Watch the motion! :D
2016-04-14 add some files
2016-04-15 More changes to UART operations.
    Fixed an off by 1 issue for reading the floats going to the band. The
    bands also got tuned up for stopping the motors in case a PC disconnects
    too
2016-04-16 Added code to automatically pull in calibration data for each band
    This is in WAGBandCommon.h with band numbers and then in
    MPU6050WAGWrapper.cpp to include these and use these numbers
2016-04-18 maybe fix crop things so that sliders move appropriately
2016-04-19 Add some stuff
2016-04-20 Cleanup of a calibration jawn
2016-04-21 fix vibration
2016-04-23 work on speed increase
2016-04-23 put in stuff to allow ghosting capability in the backend (would need to attach to person
2016-04-24 fixed up settings page. need to verify that calibrate still works file
2016-05-12 try to get background image to show up; my CSS skills are terribly rusty
2016-05-12 fix thing part 2
2016-05-12 try to fill thing appropriately
2016-05-12 fix the damn wag band scale
2016-05-12 Add third picture
2016-05-13 add image

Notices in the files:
parts and their libraries:
SparkFun-DigitalIC: Licensing: Creative Commons ShareAlike 4.0 International - https://creativecommons.org/licenses/by-sa/4.0
